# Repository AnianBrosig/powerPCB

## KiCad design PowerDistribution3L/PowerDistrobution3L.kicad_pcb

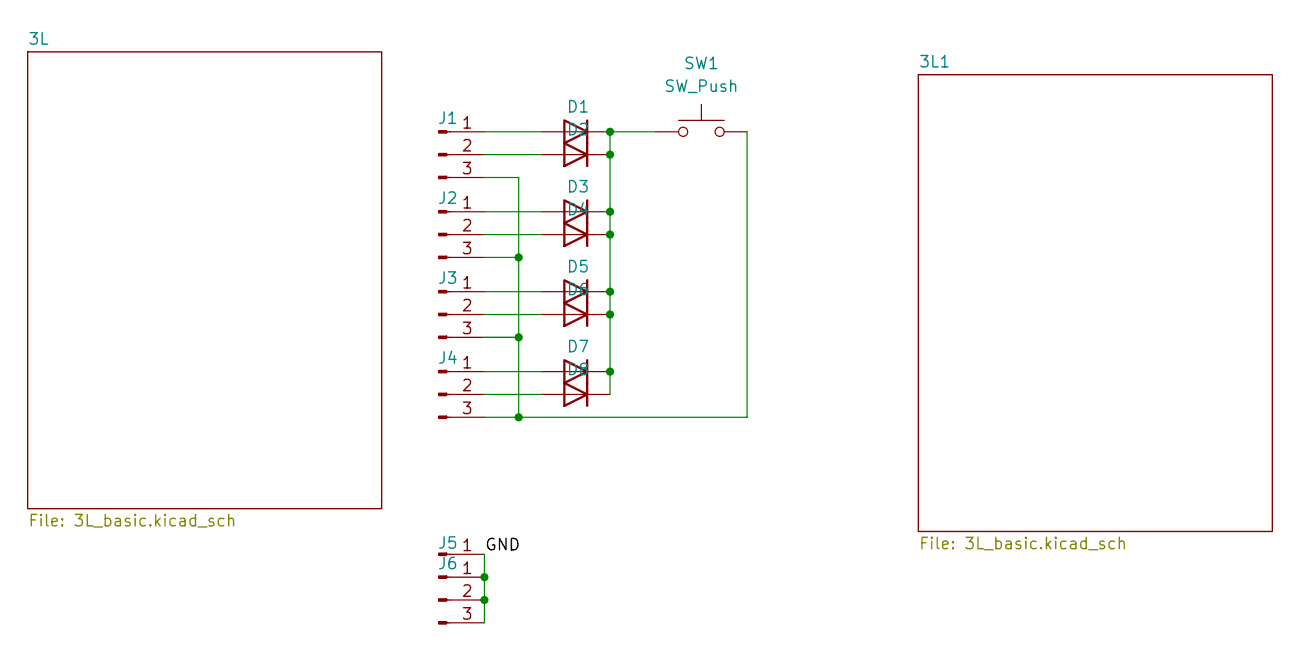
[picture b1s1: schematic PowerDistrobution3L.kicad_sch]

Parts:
D1, D2, D3, D4, D5, D6, D7, D8: 1N914; D_DO-35_SOD27_P7.62mm_Horizontal
J1, J3, J4, J6: Conn_01x03_Pin; PinHeader_1x03_P2.54mm_Vertical
J2: Connector_PinHeader_1.00mm:PinHeader_1x03_P1.00mm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; PinHeader_1x03_P2.54mm_Vertical
J5: Conn_01x01_Pin; Wuerth_REDCUBE-THR_WP-THRSH_74651175_THR
SW1: SW_Push; SW_PUSH_6mm

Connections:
/GND: J5.1, J6.1, J6.2, J6.3
unnamed: D1.2 (A), J1.1
unnamed: D1.1 (K), D2.1 (K), D3.1 (K), D4.1 (K), D5.1 (K), D6.1 (K), D7.1 (K), D8.1 (K), SW1.1
unnamed: D2.2 (A), J1.2
unnamed: D3.2 (A), J2.1
unnamed: D4.2 (A), J2.2
unnamed: D5.2 (A), J3.1
unnamed: D6.2 (A), J3.2
unnamed: D7.2 (A), J4.1
unnamed: D8.2 (A), J4.2
unnamed: J1.3, J2.3, J3.3, J4.3, SW1.2

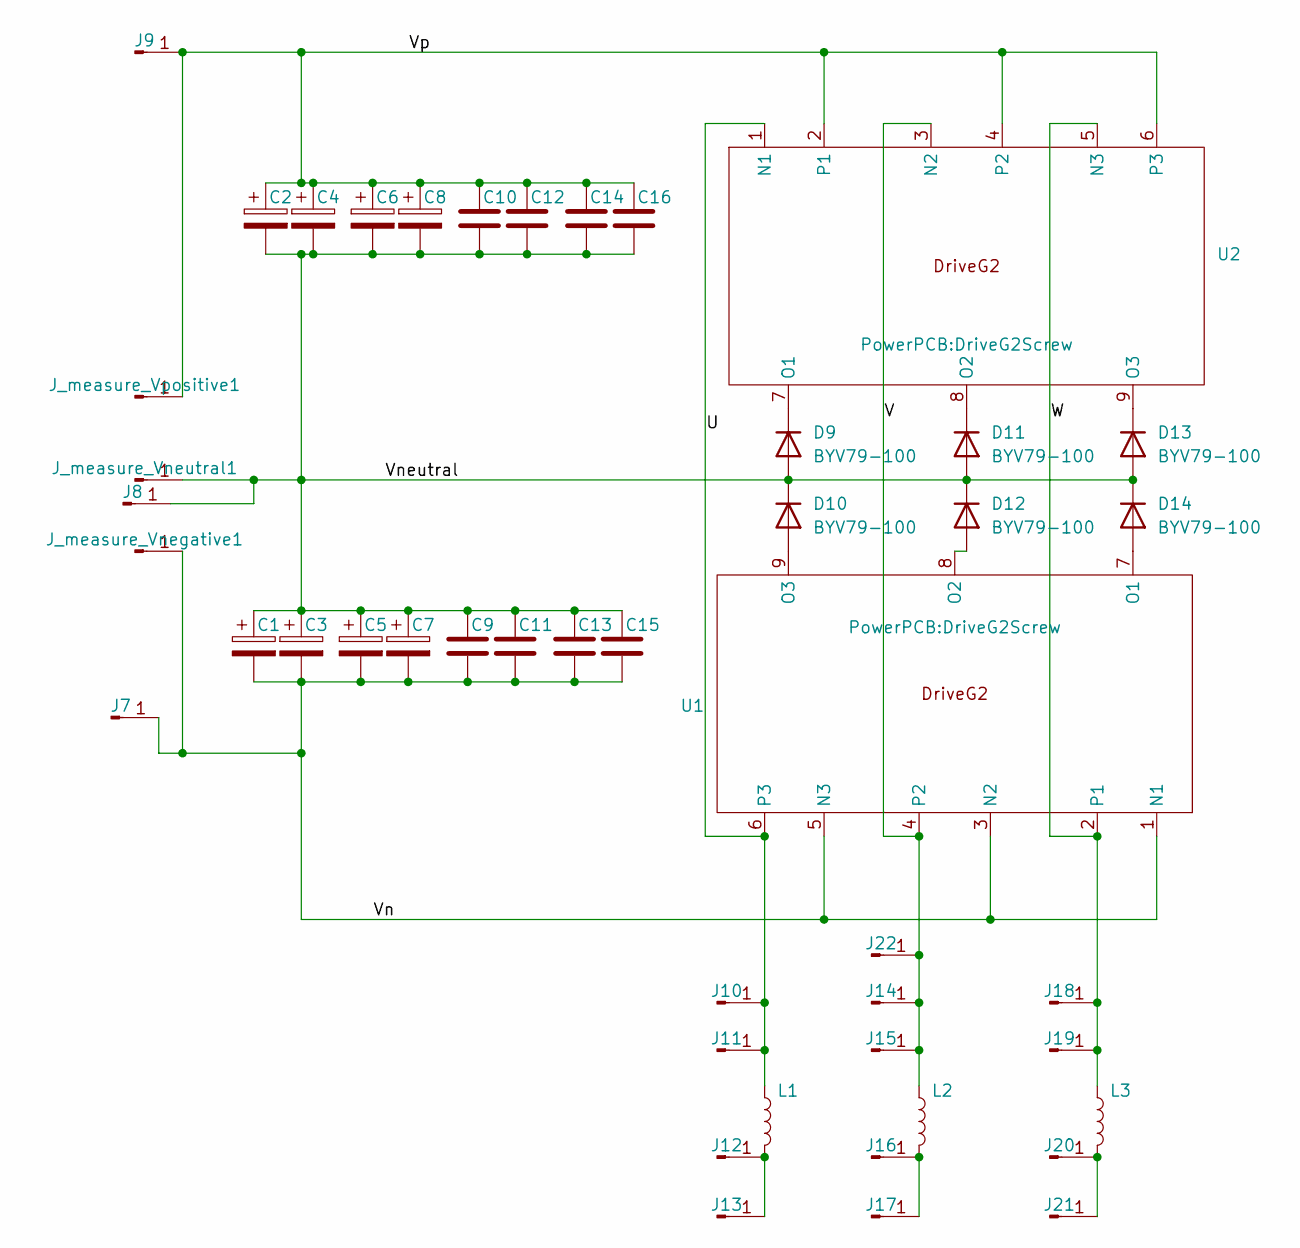
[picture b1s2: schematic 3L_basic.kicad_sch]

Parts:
C1, C2, C5, C6: C_Polarized; CP_Radial_D25.0mm_P10.00mm_SnapIn
C3, C4, C7, C8: C_Polarized; C_Wurth_WCAP-FTDB-L42W35H50
C9, C10, C11, C12, C13, C14, C15, C16: C; C_2220_5750Metric_Pad1.97x5.40mm_HandSolder
D9, D10, D11, D12, D13, D14: BYV79-100; TO-247-2_Vertical
J7, J8, J9, J10, J13, J14, J17, J18, J21, J22: Conn_01x01_Pin; Wuerth_REDCUBE-THR_WP-THRSH_74651175_THR
J11, J12, J15, J16, J19, J20: Conn_01x01_Pin; PinHeader_1x01_P1.00mm_Vertical
J_measure_Vnegative1: Conn_01x01_Pin; PinHeader_1x01_P1.00mm_Vertical
J_measure_Vneutral1: Conn_01x01_Pin; PinHeader_1x01_P1.00mm_Vertical
J_measure_Vpositive1: Conn_01x01_Pin; PinHeader_1x01_P1.00mm_Vertical
L1, L2, L3: L; Inductor
U1, U2: DriveG2Screw

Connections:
/3L/U: J10.1, J11.1, L1.1, U1.6 (P3), U2.1 (N1)
/3L/V: J14.1, J15.1, J22.1, L2.1, U1.4 (P2), U2.3 (N2)
/3L/Vn: C1.2, C3.2, C5.2, C7.2, C9.2, C11.2, C13.2, C15.2, J7.1, J_measure_Vnegative1.1, U1.1 (N1), U1.3 (N2), U1.5 (N3)
/3L/Vneutral: C1.1, C2.2, C3.1, C4.2, C5.1, C6.2, C7.1, C8.2, C9.1, C10.2, C11.1, C12.2, C13.1, C14.2, C15.1, C16.2, D9.2 (A), D10.1 (K), D11.2 (A), D12.1 (K), D13.2 (A), D14.1 (K), J8.1, J_measure_Vneutral1.1
/3L/Vp: C2.1, C4.1, C6.1, C8.1, C10.1, C12.1, C14.1, C16.1, J9.1, J_measure_Vpositive1.1, U2.2 (P1), U2.4 (P2), U2.6 (P3)
/3L/W: J18.1, J19.1, L3.1, U1.2 (P1), U2.5 (N3)
unnamed: D9.1 (K), U2.7 (O1)
unnamed: D10.2 (A), U1.9 (O3)
unnamed: D11.1 (K), U2.8 (O2)
unnamed: D12.2 (A), U1.8 (O2)
unnamed: D13.1 (K), U2.9 (O3)
unnamed: D14.2 (A), U1.7 (O1)
unnamed: J12.1, J13.1, L1.2
unnamed: J16.1, J17.1, L2.2
unnamed: J20.1, J21.1, L3.2

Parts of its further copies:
C17, C18, C21, C22: C_Polarized; CP_Radial_D25.0mm_P10.00mm_SnapIn
C19, C20, C23, C24: C_Polarized; C_Wurth_WCAP-FTDB-L42W35H50
C25, C26, C27, C28, C29, C30, C31, C32: C; C_2220_5750Metric_Pad1.97x5.40mm_HandSolder
D15, D16, D17, D18, D19, D20: BYV79-100; TO-247-2_Vertical
J23, J24, J25, J26, J29, J30, J31, J34, J35, J38: Conn_01x01_Pin; Wuerth_REDCUBE-THR_WP-THRSH_74651175_THR
J27, J28, J32, J33, J36, J37: Conn_01x01_Pin; PinHeader_1x01_P1.00mm_Vertical
J_measure_Vnegative2: Conn_01x01_Pin; PinHeader_1x01_P1.00mm_Vertical
J_measure_Vneutral2: Conn_01x01_Pin; PinHeader_1x01_P1.00mm_Vertical
J_measure_Vpositive2: Conn_01x01_Pin; PinHeader_1x01_P1.00mm_Vertical
L4, L5, L6: L; Inductor
U3, U4: DriveG2Screw

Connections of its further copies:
/3L1/U: J26.1, J27.1, L4.1, U3.6 (P3), U4.1 (N1)
/3L1/V: J30.1, J31.1, J32.1, L5.1, U3.4 (P2), U4.3 (N2)
/3L1/Vn: C17.2, C19.2, C21.2, C23.2, C25.2, C27.2, C29.2, C31.2, J23.1, J_measure_Vnegative2.1, U3.1 (N1), U3.3 (N2), U3.5 (N3)
/3L1/Vneutral: C17.1, C18.2, C19.1, C20.2, C21.1, C22.2, C23.1, C24.2, C25.1, C26.2, C27.1, C28.2, C29.1, C30.2, C31.1, C32.2, D15.2 (A), D16.1 (K), D17.2 (A), D18.1 (K), D19.2 (A), D20.1 (K), J24.1, J_measure_Vneutral2.1
/3L1/Vp: C18.1, C20.1, C22.1, C24.1, C26.1, C28.1, C30.1, C32.1, J25.1, J_measure_Vpositive2.1, U4.2 (P1), U4.4 (P2), U4.6 (P3)
/3L1/W: J35.1, J36.1, L6.1, U3.2 (P1), U4.5 (N3)
unnamed: D15.1 (K), U4.7 (O1)
unnamed: D16.2 (A), U3.9 (O3)
unnamed: D17.1 (K), U4.8 (O2)
unnamed: D18.2 (A), U3.8 (O2)
unnamed: D19.1 (K), U4.9 (O3)
unnamed: D20.2 (A), U3.7 (O1)
unnamed: J28.1, J29.1, L4.2
unnamed: J33.1, J34.1, L5.2
unnamed: J37.1, J38.1, L6.2

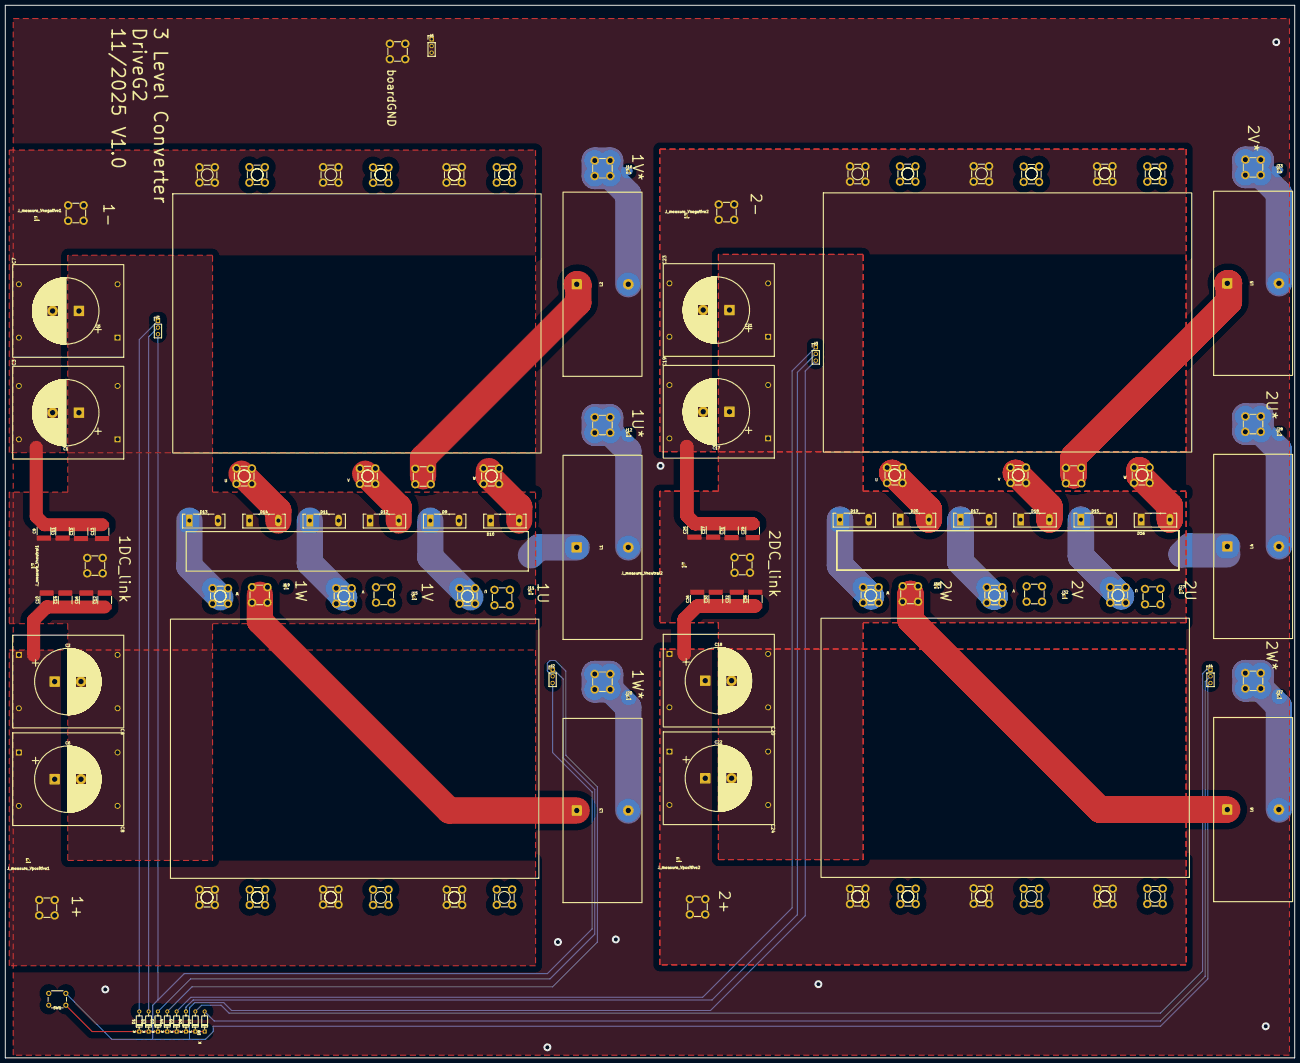
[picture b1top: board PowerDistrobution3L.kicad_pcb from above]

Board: 2 copper layers, 490.0 x 400.0 mm, 107 parts (0 on the bottom side), 41 nets.

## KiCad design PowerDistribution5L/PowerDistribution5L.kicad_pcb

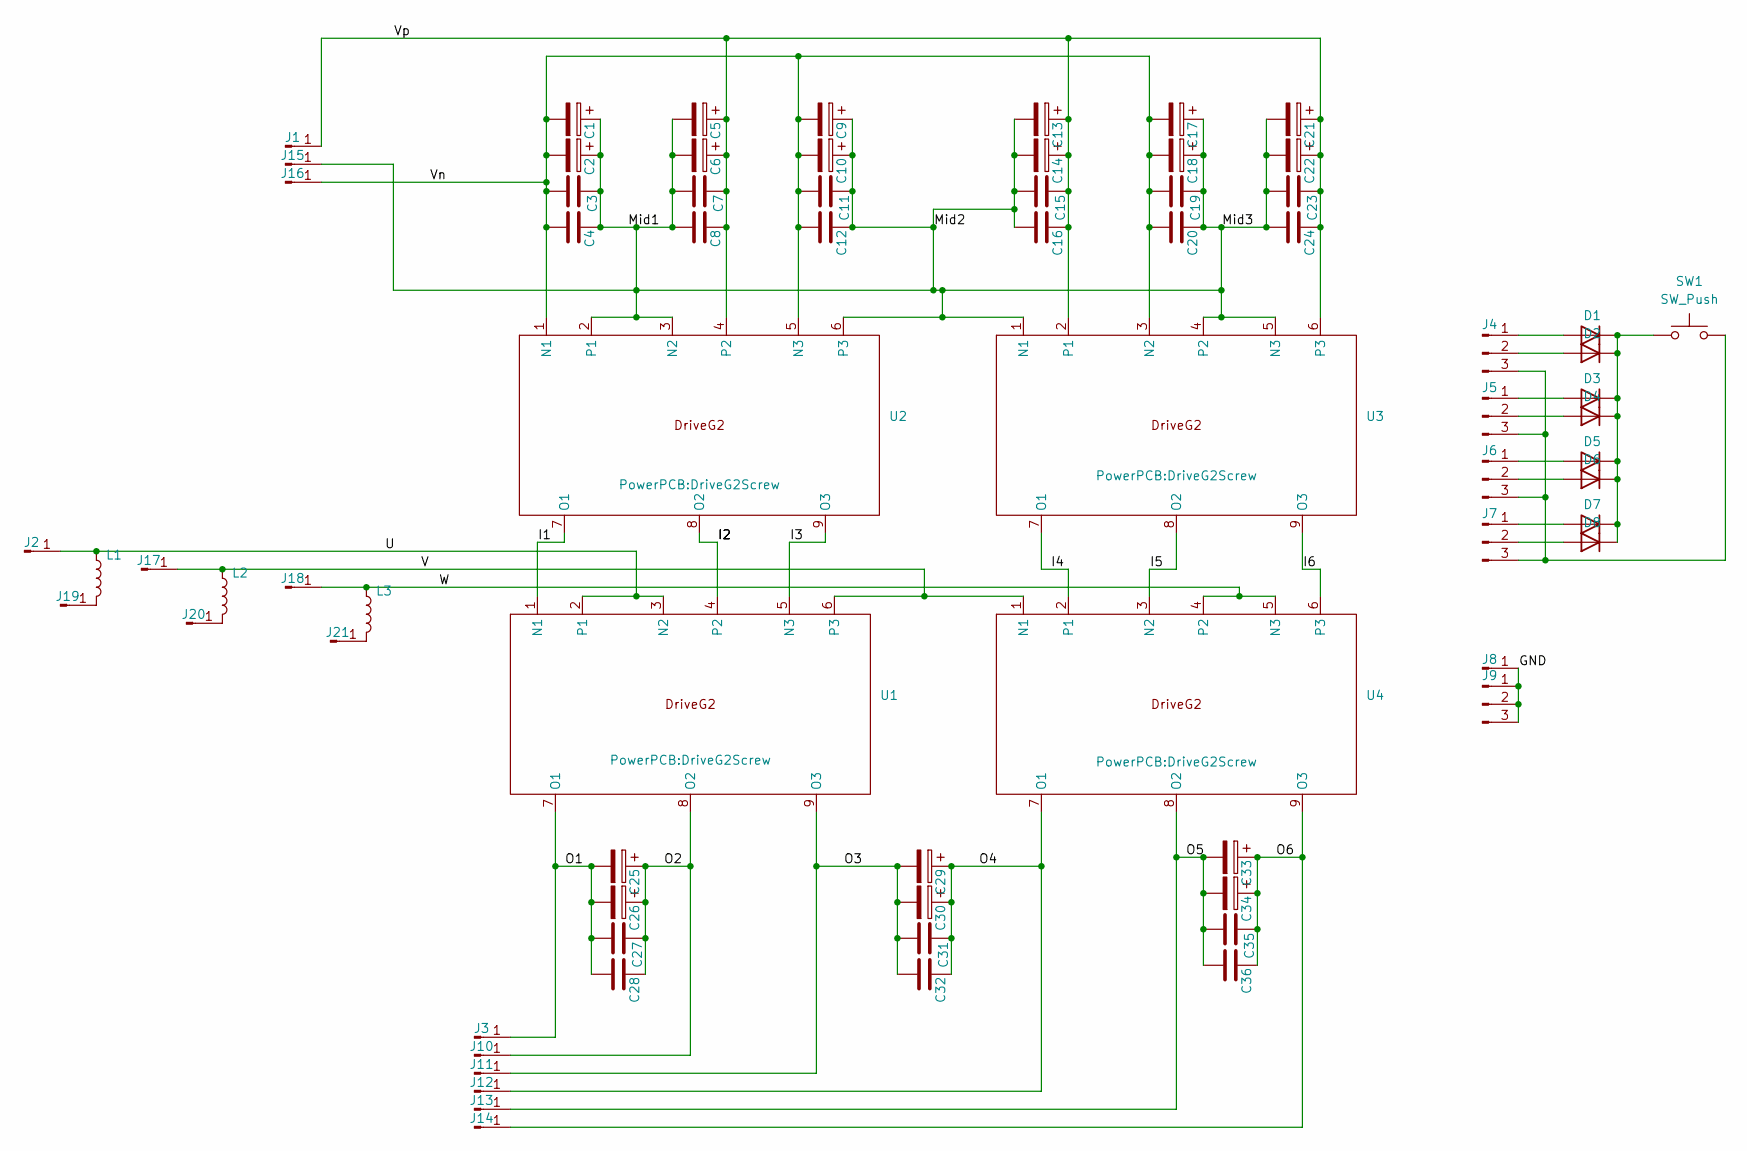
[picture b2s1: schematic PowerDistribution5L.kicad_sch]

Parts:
C1, C5, C9, C13, C17, C21, C25, C29, C33: C_Polarized; CP_Radial_D25.0mm_P10.00mm_SnapIn
C2, C6, C10, C14, C18, C22, C26, C30, C34: C_Polarized; C_Wurth_WCAP-FTDB-L42W35H50
C3, C4, C7, C8, C11, C12, C15, C16, C19, C20, C23, C24, C27, C28, C31, C32, C35, C36: C; C_2220_5750Metric_Pad1.97x5.40mm_HandSolder
D1, D2, D3, D4, D5, D6, D7, D8: 1N914; D_DO-35_SOD27_P7.62mm_Horizontal
J1, J2, J3, J8, J10, J11, J12, J13, J14, J15, J16, J17, J18, J19, J20, J21: Conn_01x01_Pin; Wuerth_REDCUBE-THR_WP-THRSH_74651175_THR
J4, J6, J7, J9: Conn_01x03_Pin; PinHeader_1x03_P2.54mm_Vertical
J5: Connector_PinHeader_1.00mm:PinHeader_1x03_P1.00mm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; PinHeader_1x03_P2.54mm_Vertical
L1, L2, L3: L; Inductor
SW1: SW_Push; SW_PUSH_6mm
U1, U2, U3, U4: DriveG2Screw

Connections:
/GND: J8.1, J9.1, J9.2, J9.3
/I1: U1.1 (N1), U2.7 (O1)
/I2: U1.4 (P2), U2.8 (O2)
/I3: U1.5 (N3), U2.9 (O3)
/I4: U3.7 (O1), U4.2 (P1)
/I5: U3.8 (O2), U4.3 (N2)
/I6: U3.9 (O3), U4.6 (P3)
/Mid1: C1.1, C2.1, C3.1, C4.1, C5.2, C6.2, C7.2, C8.2, C9.1, C10.1, C11.1, C12.1, C13.2, C14.2, C15.2, C16.2, C17.1, C18.1, C19.1, C20.1, C21.2, C22.2, C23.2, C24.2, J15.1, U2.2 (P1), U2.3 (N2), U2.6 (P3), U3.1 (N1), U3.4 (P2), U3.5 (N3)
/O1: C25.2, C26.2, C27.2, C28.2, J3.1, U1.7 (O1)
/O2: C25.1, C26.1, C27.1, C28.1, J10.1, U1.8 (O2)
/O3: C29.2, C30.2, C31.2, C32.2, J11.1, U1.9 (O3)
/O4: C29.1, C30.1, C31.1, C32.1, J12.1, U4.7 (O1)
/O5: C33.2, C34.2, C35.2, C36.2, J13.1, U4.8 (O2)
/O6: C33.1, C34.1, C35.1, C36.1, J14.1, U4.9 (O3)
/U: J2.1, L1.1, U1.2 (P1), U1.3 (N2)
/V: J17.1, L2.1, U1.6 (P3), U4.1 (N1)
/Vn: C1.2, C2.2, C3.2, C4.2, C9.2, C10.2, C11.2, C12.2, C17.2, C18.2, C19.2, C20.2, J16.1, U2.1 (N1), U2.5 (N3), U3.3 (N2)
/Vp: C5.1, C6.1, C7.1, C8.1, C13.1, C14.1, C15.1, C16.1, C21.1, C22.1, C23.1, C24.1, J1.1, U2.4 (P2), U3.2 (P1), U3.6 (P3)
/W: J18.1, L3.1, U4.4 (P2), U4.5 (N3)
unnamed: D1.2 (A), J4.1
unnamed: D1.1 (K), D2.1 (K), D3.1 (K), D4.1 (K), D5.1 (K), D6.1 (K), D7.1 (K), D8.1 (K), SW1.1
unnamed: D2.2 (A), J4.2
unnamed: D3.2 (A), J5.1
unnamed: D4.2 (A), J5.2
unnamed: D5.2 (A), J6.1
unnamed: D6.2 (A), J6.2
unnamed: D7.2 (A), J7.1
unnamed: D8.2 (A), J7.2
unnamed: J4.3, J5.3, J6.3, J7.3, SW1.2
unnamed: J19.1, L1.2
unnamed: J20.1, L2.2
unnamed: J21.1, L3.2

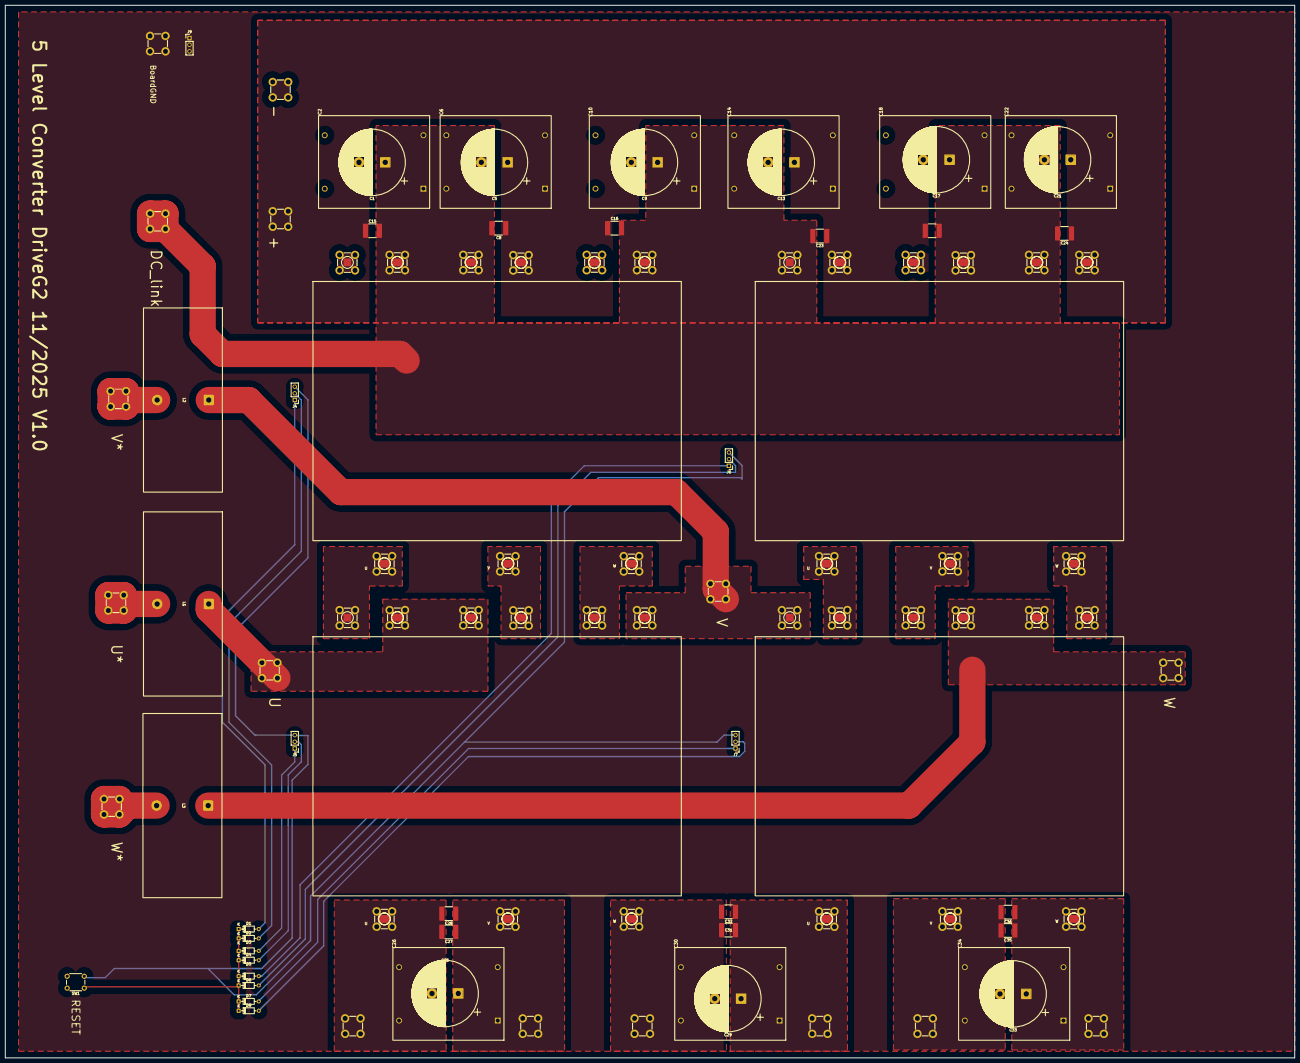
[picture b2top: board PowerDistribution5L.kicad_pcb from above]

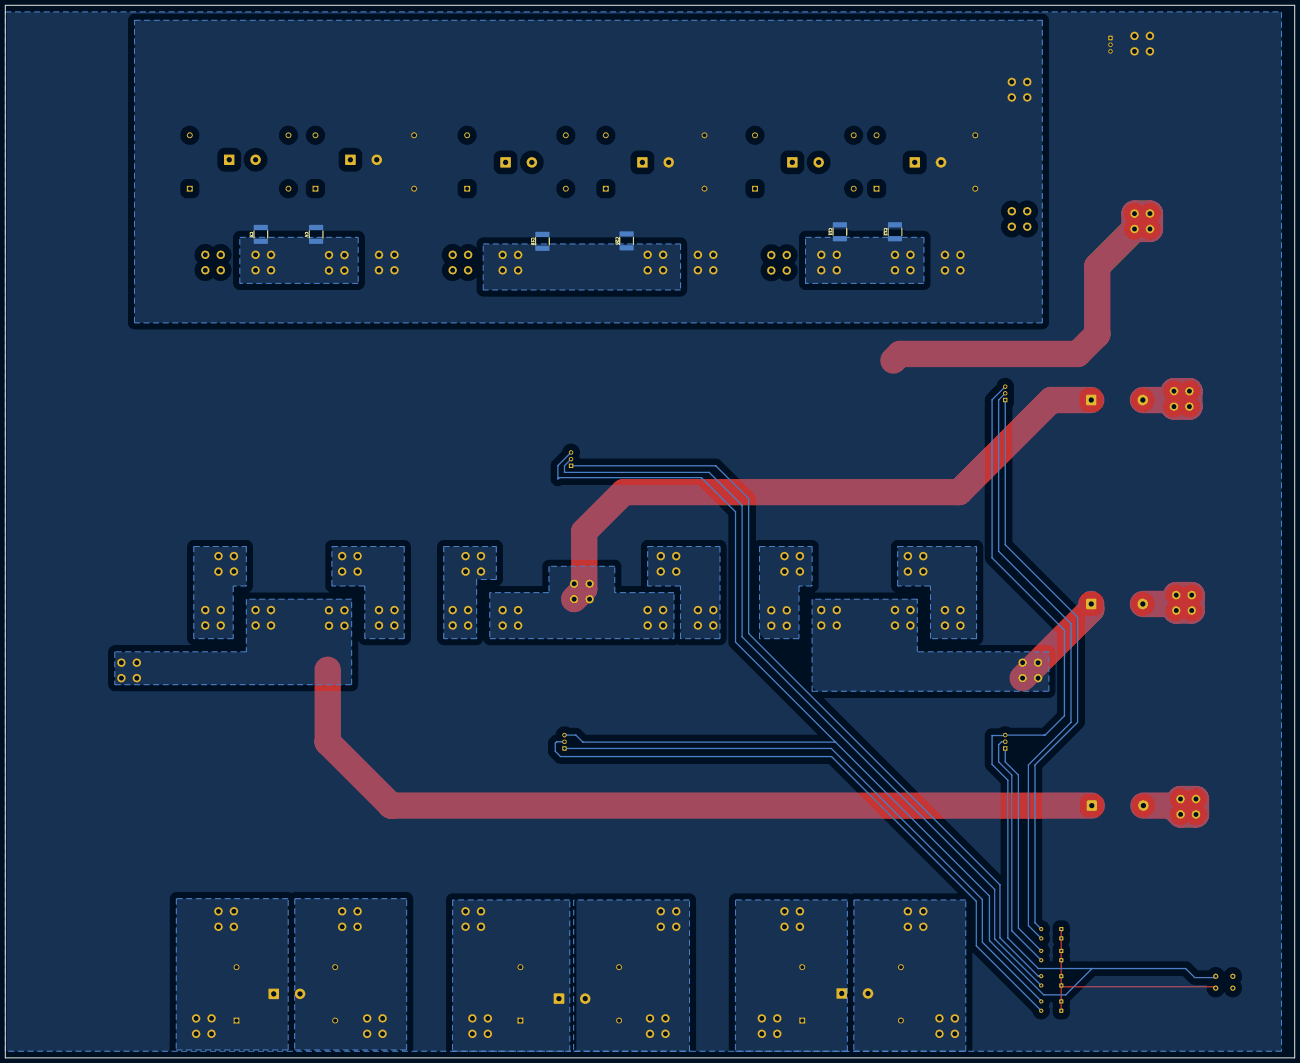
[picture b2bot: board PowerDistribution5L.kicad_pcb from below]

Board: 2 copper layers, 490.0 x 400.0 mm, 73 parts (6 on the bottom side), 32 nets.

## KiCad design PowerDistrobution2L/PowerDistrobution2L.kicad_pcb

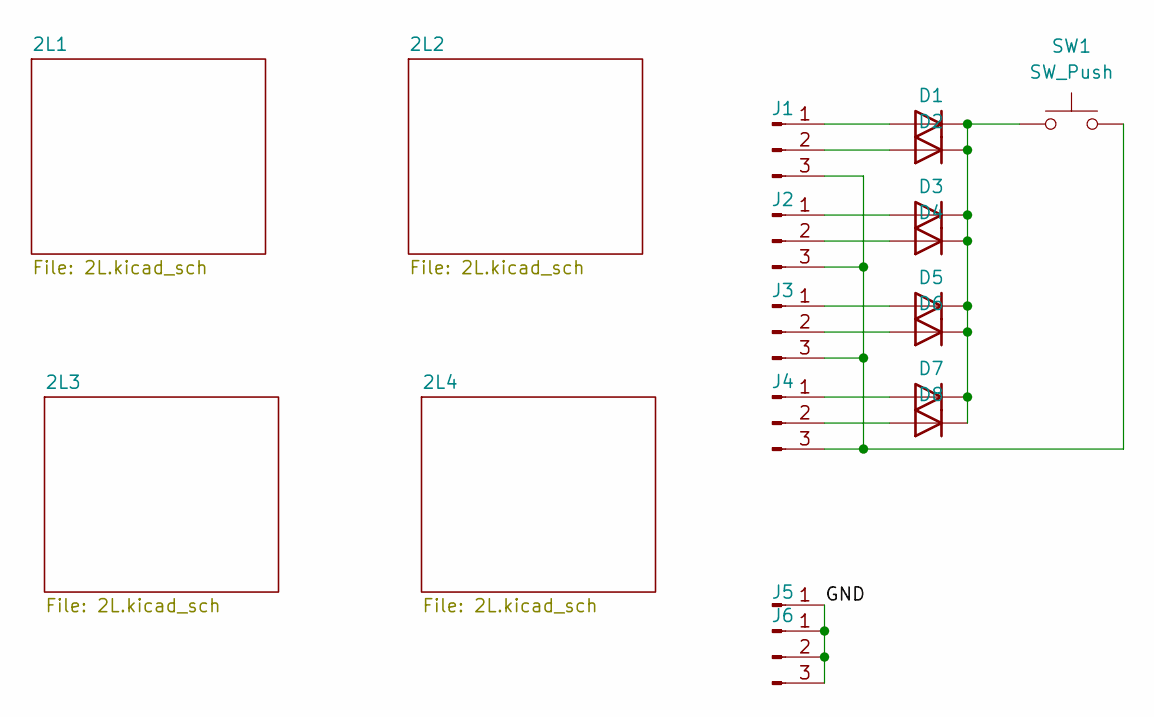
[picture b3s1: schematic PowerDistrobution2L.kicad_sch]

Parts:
D1, D2, D3, D4, D5, D6, D7, D8: 1N914; D_DO-35_SOD27_P7.62mm_Horizontal
J1, J3, J4, J6: Conn_01x03_Pin; PinHeader_1x03_P2.54mm_Vertical
J2: Connector_PinHeader_1.00mm:PinHeader_1x03_P1.00mm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; PinHeader_1x03_P2.54mm_Vertical
J5: Conn_01x01_Pin; Wuerth_REDCUBE-THR_WP-THRSH_74651175_THR
SW1: SW_Push; SW_PUSH_6mm

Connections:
/GND: J5.1, J6.1, J6.2, J6.3
unnamed: D1.2 (A), J1.1
unnamed: D1.1 (K), D2.1 (K), D3.1 (K), D4.1 (K), D5.1 (K), D6.1 (K), D7.1 (K), D8.1 (K), SW1.1
unnamed: D2.2 (A), J1.2
unnamed: D3.2 (A), J2.1
unnamed: D4.2 (A), J2.2
unnamed: D5.2 (A), J3.1
unnamed: D6.2 (A), J3.2
unnamed: D7.2 (A), J4.1
unnamed: D8.2 (A), J4.2
unnamed: J1.3, J2.3, J3.3, J4.3, SW1.2

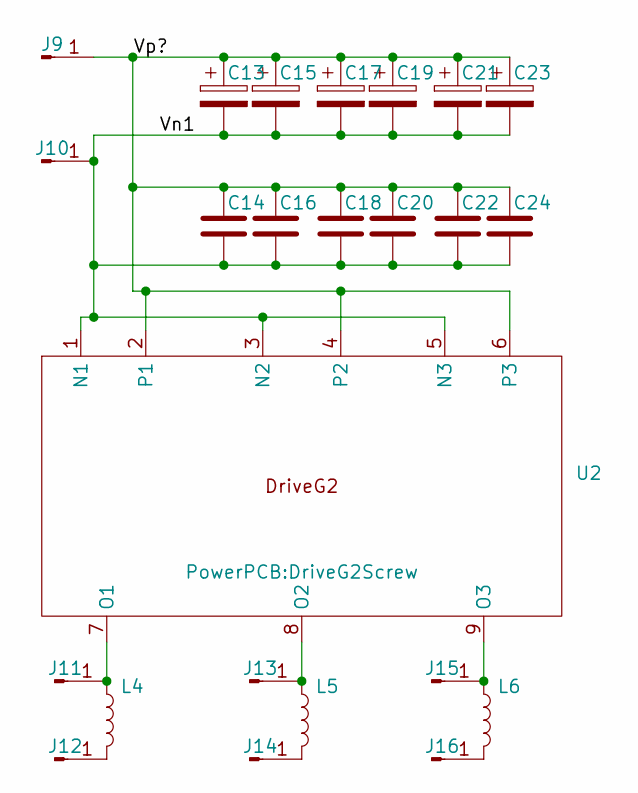
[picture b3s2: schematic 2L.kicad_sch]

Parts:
C13, C17, C21: C_Polarized; CP_Radial_D25.0mm_P10.00mm_SnapIn
C14, C16, C18, C20, C22, C24: C; C_2220_5750Metric_Pad1.97x5.40mm_HandSolder
C15, C19, C23: C_Polarized; C_Wurth_WCAP-FTDB-L42W35H50
J9, J10, J11, J12, J13, J14, J15, J16: Conn_01x01_Pin; Wuerth_REDCUBE-THR_WP-THRSH_74651175_THR
L4, L5, L6: L; Inductor
U2: DriveG2Screw

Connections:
/2L1/Vn1: C13.2, C14.2, C15.2, C16.2, C17.2, C18.2, C19.2, C20.2, C21.2, C22.2, C23.2, C24.2, J10.1, U2.1 (N1), U2.3 (N2), U2.5 (N3)
/2L1/Vp?: C13.1, C14.1, C15.1, C16.1, C17.1, C18.1, C19.1, C20.1, C21.1, C22.1, C23.1, C24.1, J9.1, U2.2 (P1), U2.4 (P2), U2.6 (P3)
unnamed: J11.1, L4.1, U2.7 (O1)
unnamed: J12.1, L4.2
unnamed: J13.1, L5.1, U2.8 (O2)
unnamed: J14.1, L5.2
unnamed: J15.1, L6.1, U2.9 (O3)
unnamed: J16.1, L6.2

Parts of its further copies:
C25, C29, C33, C37, C41, C45, C49, C53, C57: C_Polarized; CP_Radial_D25.0mm_P10.00mm_SnapIn
C26, C28, C30, C32, C34, C36, C38, C40, C42, C44, C46, C48, C50, C52, C54, C56, C58, C60: C; C_2220_5750Metric_Pad1.97x5.40mm_HandSolder
C27, C31, C35, C39, C43, C47, C51, C55, C59: C_Polarized; C_Wurth_WCAP-FTDB-L42W35H50
J17, J18, J19, J20, J21, J22, J23, J24, J25, J26, J27, J29, J31, J33, J34, J35, J37, J39: Conn_01x01_Pin; Wuerth_REDCUBE-THR_WP-THRSH_74651175_THR
L7, L8, L9: L; Inductor
U3, U4, U5: DriveG2Screw

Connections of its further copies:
/2L2/Vn1: C25.2, C26.2, C27.2, C28.2, C29.2, C30.2, C31.2, C32.2, C33.2, C34.2, C35.2, C36.2, J18.1, U3.1 (N1), U3.3 (N2), U3.5 (N3)
/2L2/Vp?: C25.1, C26.1, C27.1, C28.1, C29.1, C30.1, C31.1, C32.1, C33.1, C34.1, C35.1, C36.1, J17.1, U3.2 (P1), U3.4 (P2), U3.6 (P3)
/2L3/Vn1: C37.2, C38.2, C39.2, C40.2, C41.2, C42.2, C43.2, C44.2, C45.2, C46.2, C47.2, C48.2, J26.1, U4.1 (N1), U4.3 (N2), U4.5 (N3)
/2L3/Vp?: C37.1, C38.1, C39.1, C40.1, C41.1, C42.1, C43.1, C44.1, C45.1, C46.1, C47.1, C48.1, J25.1, U4.2 (P1), U4.4 (P2), U4.6 (P3)
/2L4/Vn1: C49.2, C50.2, C51.2, C52.2, C53.2, C54.2, C55.2, C56.2, C57.2, C58.2, C59.2, C60.2, J34.1, U5.1 (N1), U5.3 (N2), U5.5 (N3)
/2L4/Vp?: C49.1, C50.1, C51.1, C52.1, C53.1, C54.1, C55.1, C56.1, C57.1, C58.1, C59.1, C60.1, J33.1, U5.2 (P1), U5.4 (P2), U5.6 (P3)
unnamed: J19.1, L7.1, U3.7 (O1)
unnamed: J20.1, L7.2
unnamed: J21.1, L8.1, U3.8 (O2)
unnamed: J22.1, L8.2
unnamed: J23.1, L9.1, U3.9 (O3)
unnamed: J24.1, L9.2
unnamed: J27.1, U4.7 (O1)
unnamed: J29.1, U4.8 (O2)
unnamed: J31.1, U4.9 (O3)
unnamed: J35.1, U5.7 (O1)
unnamed: J37.1, U5.8 (O2)
unnamed: J39.1, U5.9 (O3)

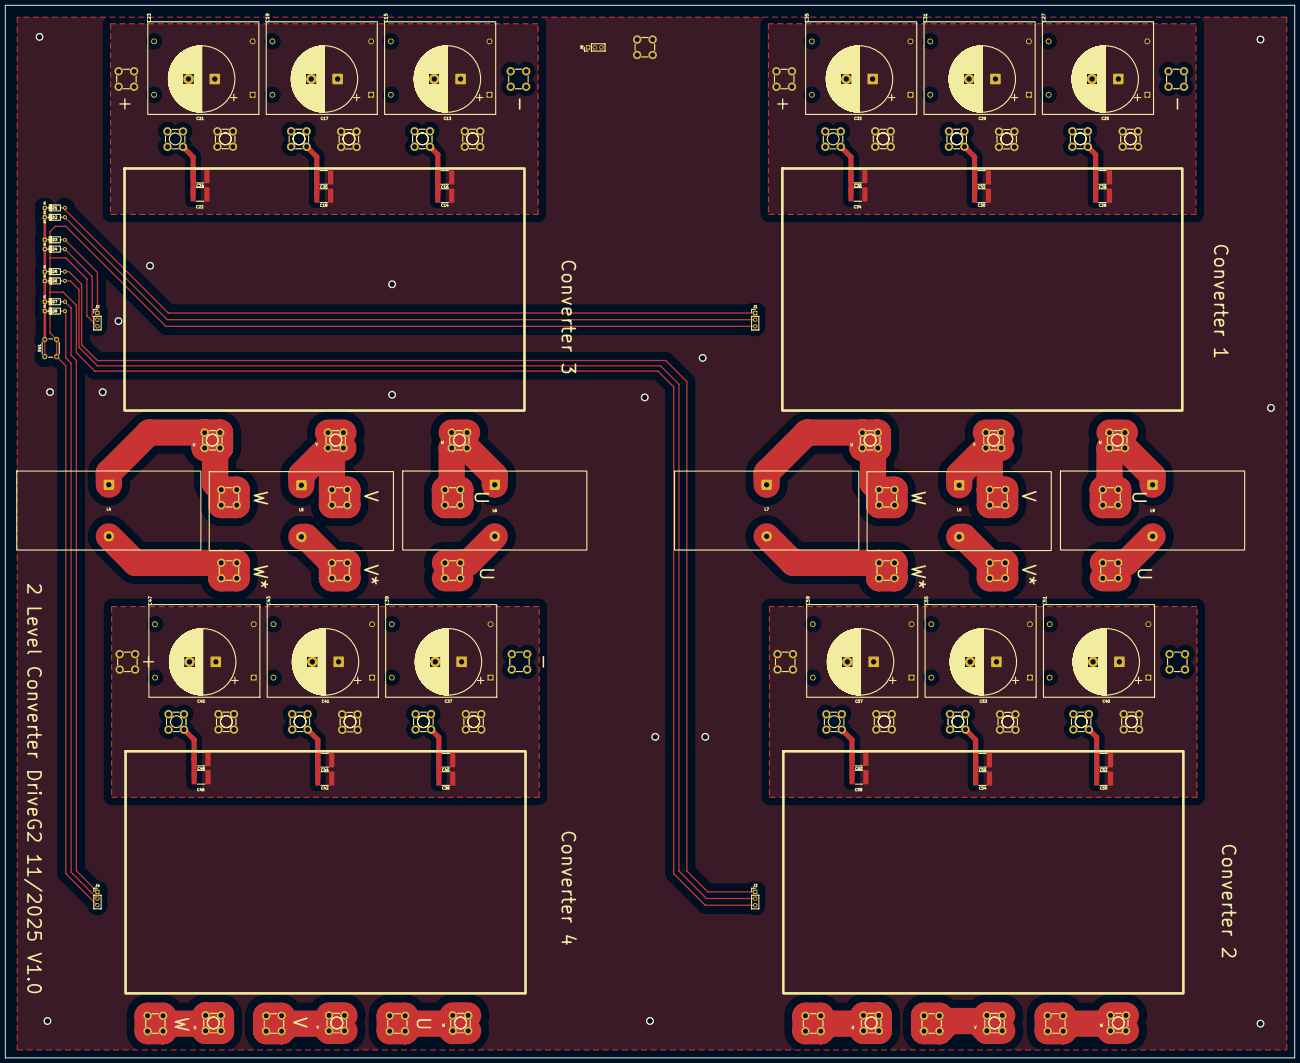
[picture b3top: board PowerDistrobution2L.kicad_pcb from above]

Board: 2 copper layers, 490.0 x 400.0 mm, 99 parts (0 on the bottom side), 37 nets.

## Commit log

2025-11-11 2L Initial
2025-11-13 add 3 Level and 5 Level
2025-11-18 ProductionFiles
